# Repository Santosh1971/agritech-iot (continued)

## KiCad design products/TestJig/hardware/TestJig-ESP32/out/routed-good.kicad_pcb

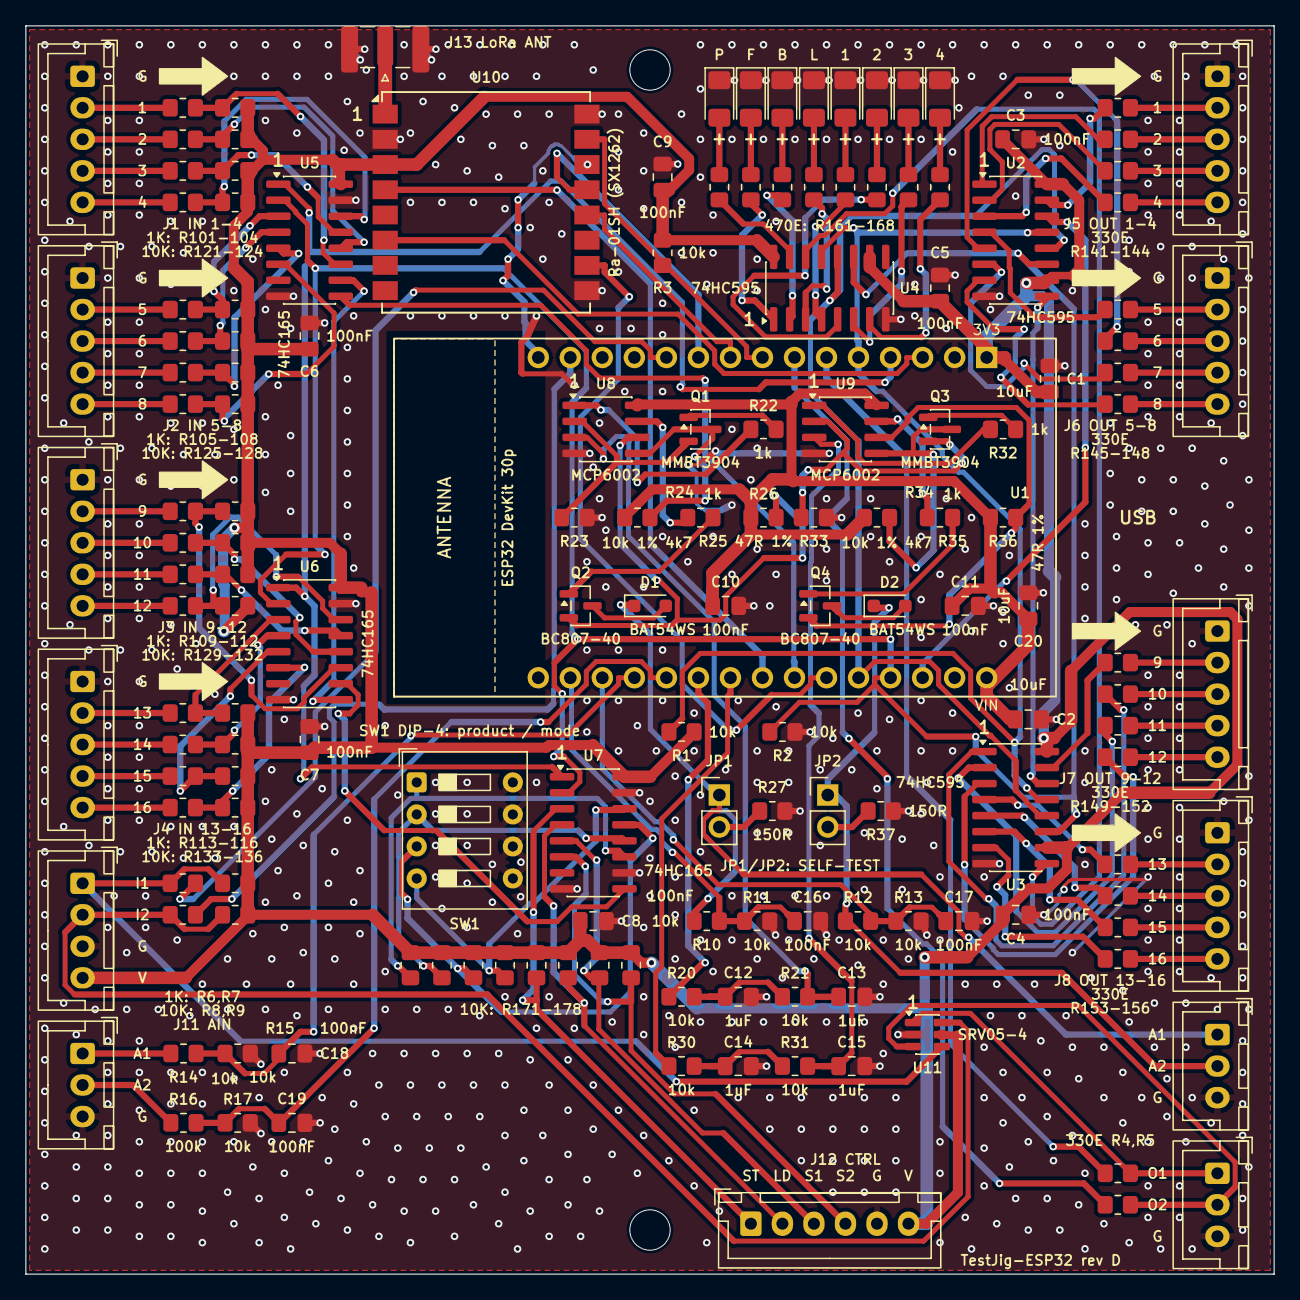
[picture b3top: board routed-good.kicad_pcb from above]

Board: 2 copper layers, 99.0 x 99.0 mm, 161 parts (0 on the bottom side), 149 nets.

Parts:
C1, C2, C20: 10uF; C_0805_2012Metric_Pad1.18x1.45mm_HandSolder
C3, C4, C5, C6, C7, C8, C9, C10, C11, C16, C17, C18, C19: 100nF; C_0805_2012Metric_Pad1.18x1.45mm_HandSolder
C12, C13, C14, C15: 1uF; C_0805_2012Metric_Pad1.18x1.45mm_HandSolder
D1, D2: BAT54WS; D_SOD-323_HandSoldering
D7: PASS Green; LED_1206_3216Metric_Pad1.42x1.75mm_HandSolder
D8: FAIL Red; LED_1206_3216Metric_Pad1.42x1.75mm_HandSolder
D9: BUSY Yellow; LED_1206_3216Metric_Pad1.42x1.75mm_HandSolder
D10: LORA Blue; LED_1206_3216Metric_Pad1.42x1.75mm_HandSolder
D11: USER1 Green; LED_1206_3216Metric_Pad1.42x1.75mm_HandSolder
D12: USER2 Green; LED_1206_3216Metric_Pad1.42x1.75mm_HandSolder
D13: USER3 Green; LED_1206_3216Metric_Pad1.42x1.75mm_HandSolder
D14: USER4 Green; LED_1206_3216Metric_Pad1.42x1.75mm_HandSolder
H1, H2: M3; MountingHole_3.2mm_M3
J1: RLY_SENSE 1-4; JST_XH_B5B-XH-A_1x05_P2.50mm_Vertical
J2: RLY_SENSE 5-8; JST_XH_B5B-XH-A_1x05_P2.50mm_Vertical
J3: RLY_SENSE 9-12; JST_XH_B5B-XH-A_1x05_P2.50mm_Vertical
J4: RLY_SENSE 13-16; JST_XH_B5B-XH-A_1x05_P2.50mm_Vertical
J5: DUT_IN 1-4; JST_XH_B5B-XH-A_1x05_P2.50mm_Vertical
J6: DUT_IN 5-8; JST_XH_B5B-XH-A_1x05_P2.50mm_Vertical
J7: DUT_IN 9-12; JST_XH_B5B-XH-A_1x05_P2.50mm_Vertical
J8: DUT_IN 13-16; JST_XH_B5B-XH-A_1x05_P2.50mm_Vertical
J9: PULSE IN; JST_XH_B4B-XH-A_1x04_P2.50mm_Vertical
J10: 4-20mA OUT; JST_XH_B3B-XH-A_1x03_P2.50mm_Vertical
J11: AIN (AI1 /2, AI2 /11); JST_XH_B3B-XH-A_1x03_P2.50mm_Vertical
J12: JIG_CTRL; JST_XH_B6B-XH-A_1x06_P2.50mm_Vertical
J13: SMA; SMA_Samtec_SMA-J-P-H-ST-EM1_EdgeMount
J14: PULSE OUT; JST_XH_B3B-XH-A_1x03_P2.50mm_Vertical
JP1, JP2: SELFTEST; PinHeader_1x02_P2.54mm_Vertical
Q1, Q3: MMBT3904; SOT-23
Q2, Q4: BC807-40; SOT-23
R1, R2, R3, R8, R9, R10, R11, R12, R13, R14, R15, R17, R20, R21, R30, R31, R121, R122, R123, R124, R125, R126, R127, R128, R129, R130, R131, R132, R133, R134, R135, R136, R171, R172, R173, R174, R175, R176, R177, R178: 10k; R_0805_2012Metric_Pad1.20x1.40mm_HandSolder
R4, R5, R141, R142, R143, R144, R145, R146, R147, R148, R149, R150, R151, R152, R153, R154, R155, R156: 330; R_0805_2012Metric_Pad1.20x1.40mm_HandSolder
R6, R7, R22, R25, R32, R35, R101, R102, R103, R104, R105, R106, R107, R108, R109, R110, R111, R112, R113, R114, R115, R116: 1k; R_0805_2012Metric_Pad1.20x1.40mm_HandSolder
R16: 100k; R_0805_2012Metric_Pad1.20x1.40mm_HandSolder
R23, R33: 10k 1%; R_0805_2012Metric_Pad1.20x1.40mm_HandSolder
R24, R34: 4k7; R_0805_2012Metric_Pad1.20x1.40mm_HandSolder
R26, R36: 47R 1%; R_0805_2012Metric_Pad1.20x1.40mm_HandSolder
R27, R37: 150R; R_0805_2012Metric_Pad1.20x1.40mm_HandSolder
R161, R162, R163, R164, R165, R166, R167, R168: 470; R_0805_2012Metric_Pad1.20x1.40mm_HandSolder
SW1: DIP-4; SW_DIP_SPSTx04_Slide_9.78x12.34mm_W7.62mm_P2.54mm
U1: ESP32 DevKit 30p; ESP32_DevKit_30pin_W25.4mm
U2, U3, U4: 74HC595; SOIC-16_3.9x9.9mm_P1.27mm
U5, U6, U7: 74HC165; SOIC-16_3.9x9.9mm_P1.27mm
U8, U9: MCP6002; SOIC-8_3.9x4.9mm_P1.27mm
U10: Ra-01SH (SX1262); Ai-Thinker-Ra-01-LoRa
U11: SRV05-4; SOT-23-6

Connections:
+3V3: C1.1, C3.1, C4.1, C5.1, C6.1, C7.1, C8.1, C9.1, J9.4, J12.6, R1.2, R3.2, R8.2, R9.2, R121.2, R122.2, R123.2, R124.2, R125.2, R126.2, R127.2, R128.2, R129.2, R130.2, R131.2, R132.2, R133.2, R134.2, R135.2, R136.2, R171.2, R172.2, R173.2, R174.2, R175.2, R176.2, R177.2, R178.2, U1.1, U2.10, U2.16, U3.10, U3.16, U4.10, U4.16, U5.16, U6.16, U7.16, U10.3, U11.5
+5V: C2.1, C10.1, C11.1, C20.1, R24.1, R26.1, R34.1, R36.1, U1.30, U8.8, U9.8
/ADC_AI1: C18.1, R14.2, R15.1, U1.19
/ADC_AI2: C19.1, R16.2, R17.1, U1.20
/ADC_AO1: C16.1, R10.2, R11.1, U1.17
/ADC_AO2: C17.1, R12.2, R13.1, U1.18
/AI1: J11.1, R14.1
/AI2: J11.2, R16.1
/AO1: D1.1, J10.1, JP1.1, R10.1
/AO1_A: Q1.3, R24.2, U8.5
/AO1_B: Q2.2, R26.2, U8.6
/AO1_F1: C12.1, R20.2, R21.1
/AO1_LOAD: JP1.2, R27.1
/AO1_QB1: Q1.1, R22.2
/AO1_QB2: Q2.1, R25.2
/AO1_QC: D1.2, Q2.3
/AO1_QE: Q1.2, R23.1, U8.2
/AO1_U1: R22.1, U8.1
/AO1_U2: R25.1, U8.7
/AO1_VSET: C13.1, R21.2, U8.3
/AO2: D2.1, J10.2, JP2.1, R12.1
/AO2_A: Q3.3, R34.2, U9.5
/AO2_B: Q4.2, R36.2, U9.6
/AO2_F1: C14.1, R30.2, R31.1
/AO2_LOAD: JP2.2, R37.1
/AO2_QB1: Q3.1, R32.2
/AO2_QB2: Q4.1, R35.2
/AO2_QC: D2.2, Q4.3
/AO2_QE: Q3.2, R33.1, U9.2
/AO2_U1: R32.1, U9.1
/AO2_U2: R35.1, U9.7
/AO2_VSET: C15.1, R31.2, U9.3
/DIP1: R171.1, SW1.1, U7.11
/DIP2: R172.1, SW1.2, U7.12
/DIP3: R173.1, SW1.3, U7.13
/DIP4: R174.1, SW1.4, U7.14
/DO1: R141.1, U2.15
/DO2: R142.1, U2.1
/DO3: R143.1, U2.2
/DO4: R144.1, U2.3
/DO5: R145.1, U2.4
/DO6: R146.1, U2.5
/DO7: R147.1, U2.6
/DO8: R148.1, U2.7
/DO9: R149.1, U3.15
/DO10: R150.1, U3.1
/DO11: R151.1, U3.2
/DO12: R152.1, U3.3
/DO13: R153.1, U3.4
/DO14: R154.1, U3.5
/DO15: R155.1, U3.6
/DO16: R156.1, U3.7
/DUT_OUT1: J5.2, R141.2
/DUT_OUT2: J5.3, R142.2
/DUT_OUT3: J5.4, R143.2
/DUT_OUT4: J5.5, R144.2
/DUT_OUT5: J6.2, R145.2
/DUT_OUT6: J6.3, R146.2
/DUT_OUT7: J6.4, R147.2
/DUT_OUT8: J6.5, R148.2
/DUT_OUT9: J7.2, R149.2
/DUT_OUT10: J7.3, R150.2
/DUT_OUT11: J7.4, R151.2
/DUT_OUT12: J7.5, R152.2
/DUT_OUT13: J8.2, R153.2
/DUT_OUT14: J8.3, R154.2
/DUT_OUT15: J8.4, R155.2
/DUT_OUT16: J8.5, R156.2
/LEDA1: D7.2, R161.2
/LEDA2: D8.2, R162.2
/LEDA3: D9.2, R163.2
/LEDA4: D10.2, R164.2
/LEDA5: D11.2, R165.2
/LEDA6: D12.2, R166.2
/LEDA7: D13.2, R167.2
/LEDA8: D14.2, R168.2
/LEDDRV1: R161.1, U4.15
/LEDDRV2: R162.1, U4.1
/LEDDRV3: R163.1, U4.2
/LEDDRV4: R164.1, U4.3
/LEDDRV5: R165.1, U4.4
/LEDDRV6: R166.1, U4.5
/LEDDRV7: R167.1, U4.6
/LEDDRV8: R168.1, U4.7
/LID: J12.2, R176.1, U7.4
/LORA_ANT: J13.1, U10.1
/LORA_BUSY: U1.25, U10.10
/LORA_DIO1: U1.3, U10.6
/LORA_NSS: R3.1, U1.8, U10.15
/LORA_RST: U1.23, U10.4
/PI1: R6.2, U1.11
/PI2: R7.2, U1.14
/PO1: R4.1, U1.6
/PO2: R5.1, U1.7
/PULSE_IN1: J9.1, R6.1, R8.1, U11.4
/PULSE_IN2: J9.2, R7.1, R9.1, U11.6
/PULSE_OUT1: J14.1, R4.2, U11.1
/PULSE_OUT2: J14.2, R5.2, U11.3
/PWM_AO1: R20.1, U1.21
/PWM_AO2: R30.1, U1.22
/RLY_NO1: J1.2, R101.1
/RLY_NO2: J1.3, R102.1
/RLY_NO3: J1.4, R103.1
/RLY_NO4: J1.5, R104.1
/RLY_NO5: J2.2, R105.1
/RLY_NO6: J2.3, R106.1
/RLY_NO7: J2.4, R107.1
/RLY_NO8: J2.5, R108.1
/RLY_NO9: J3.2, R109.1
/RLY_NO10: J3.3, R110.1
/RLY_NO11: J3.4, R111.1
/RLY_NO12: J3.5, R112.1
/RLY_NO13: J4.2, R113.1
/RLY_NO14: J4.3, R114.1
/RLY_NO15: J4.4, R115.1
/RLY_NO16: J4.5, R116.1
/RS1: R101.2, R121.1, U5.11
/RS2: R102.2, R122.1, U5.12
/RS3: R103.2, R123.1, U5.13
/RS4: R104.2, R124.1, U5.14
/RS5: R105.2, R125.1, U5.3
/RS6: R106.2, R126.1, U5.4
/RS7: R107.2, R127.1, U5.5
/RS8: R108.2, R128.1, U5.6
/RS9: R109.2, R129.1, U6.11
/RS10: R110.2, R130.1, U6.12
/RS11: R111.2, R131.1, U6.13
/RS12: R112.2, R132.1, U6.14
/RS13: R113.2, R133.1, U6.3
/RS14: R114.2, R134.1, U6.4
/RS15: R115.2, R135.1, U6.5
/RS16: R116.2, R136.1, U6.6
/SPARE_IN1: J12.3, R177.1, U7.5
/SPARE_IN2: J12.4, R178.1, U7.6
/SPI_MISO: U1.10, U10.13
/SPI_MOSI: U1.15, U10.14
/SPI_SCK: U1.9, U10.12
/SR_CLK: R2.1, U1.27, U2.11, U3.11, U4.11, U5.2, U6.2, U7.2
/SR_D2: U2.9, U3.14
/SR_D3: U3.9, U4.14
/SR_DATA: U1.28, U2.14
/SR_IN: U1.24, U5.9
/SR_LATCH: U1.26, U2.12, U3.12, U4.12
/SR_LOAD: U1.4, U5.1, U6.1, U7.1
/SR_OE: R1.1, U1.5, U2.13, U3.13, U4.13
/SR_Q6: U5.10, U6.9
/SR_Q7: U6.10, U7.9
/START: J12.1, R175.1, U7.3
GND: C1.2, C2.2, C3.2, C4.2, C5.2, C6.2, C7.2, C8.2, C9.2, C10.2, C11.2, C12.2, C13.2, C14.2, C15.2, C16.2, C17.2, C18.2, C19.2, C20.2, D7.1, D8.1, D9.1, D10.1, D11.1, D12.1, D13.1, D14.1, J1.1, J2.1, J3.1, J4.1, J5.1, J6.1, J7.1, J8.1, J9.3, J10.3, J11.3, J12.5, J13.2, J14.3, R2.2, R11.2, R13.2, R15.2, R17.2, R23.2, R27.2, R33.2, R37.2, SW1.5, SW1.6, SW1.7, SW1.8, U1.2, U1.29, U2.8, U3.8, U4.8, U5.8, U5.15, U6.8, U6.15, U7.8, U7.10, U7.15, U8.4, U9.4, U10.2, U10.9, U10.16, U11.2

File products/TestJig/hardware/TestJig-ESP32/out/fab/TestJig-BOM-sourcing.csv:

References,Qty,Value,Footprint,Supplier,Listing,Price (incl GST),Link
"C1, C2, C20",3,10uF,C_0805_2012Metric_Pad1.18x1.45mm_HandSolder,Quartz,10uF 10V X5R 0805 (Kemet),Rs 45 / 20 pcs,https://quartzcomponents.com/products/kemet-10uf-50v-0805-sm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
"C3, C4, C5, C6, C7, C8, C9, C10, C11, C16, C17, C18, C19",13,100nF,C_0805_2012Metric_Pad1.18x1.45mm_HandSolder,Quartz,100nF 50V X7R 0805 (Kemet),Rs 26 / 20 pcs,https://quartzcomponents.com/products/kemet-100nf-50v-0805-s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
"C12, C13, C14, C15",4,1uF,C_0805_2012Metric_Pad1.18x1.45mm_HandSolder,Quartz,1uF 50V X7R 0805,Rs 15 / 5 pcs,https://quartzcomponents.com/products/1uf-1000nf-50v-0805-x7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
"D1, D2",2,BAT54WS,D_SOD-323_HandSoldering,Quartz,BAT54WS SOD-323,Rs 19 / 10 pcs,https://quartzcomponents.com/products/bat54ws-small-signal-s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
D7,1,PASS Green,LED_1206_3216Metric_Pad1.42x1.75mm_HandSolder,Quartz,Green LED 1206,Rs 36 / 50 pcs,https://quartzcomponents.com/products/green-led-smd-1206-pac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
D8,1,FAIL Red,LED_1206_3216Metric_Pad1.42x1.75mm_HandSolder,Quartz,Red LED 1206,Rs 35 / 50 pcs,https://quartzcomponents.com/products/red-led-smd-1206-packa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
D9,1,BUSY Yellow,LED_1206_3216Metric_Pad1.42x1.75mm_HandSolder,Quartz,Yellow LED 1206,Rs 39 / 50 pcs,https://quartzcomponents.com/products/yellow-led-smd-1206-pa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
D10,1,LORA Blue,LED_1206_3216Metric_Pad1.42x1.75mm_HandSolder,Quartz,Blue LED 1206,Rs 32 / 50 pcs,https://quartzcomponents.com/products/blue-led-smd-1206-pack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
D11,1,USER1 Green,LED_1206_3216Metric_Pad1.42x1.75mm_HandSolder,Quartz,Green LED 1206,Rs 36 / 50 pcs,https://quartzcomponents.com/products/green-led-smd-1206-pac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
D12,1,USER2 Green,LED_1206_3216Metric_Pad1.42x1.75mm_HandSolder,Quartz,Green LED 1206,Rs 36 / 50 pcs,https://quartzcomponents.com/products/green-led-smd-1206-pac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
D13,1,USER3 Green,LED_1206_3216Metric_Pad1.42x1.75mm_HandSolder,Quartz,Green LED 1206,Rs 36 / 50 pcs,https://quartzcomponents.com/products/green-led-smd-1206-pac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
D14,1,USER4 Green,LED_1206_3216Metric_Pad1.42x1.75mm_HandSolder,Quartz,Green LED 1206,Rs 36 / 50 pcs,https://quartzcomponents.com/products/green-led-smd-1206-pac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
J1,1,RLY_SENSE 1-4,JST_XH_B5B-XH-A_1x05_P2.50mm_Vertical,Quartz,5-pin JST XH male (vertical),Rs 2 each,https://quartzcomponents.com/products/5-pin-jst-xh-male-conn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
J2,1,RLY_SENSE 5-8,JST_XH_B5B-XH-A_1x05_P2.50mm_Vertical,Quartz,5-pin JST XH male (vertical),Rs 2 each,https://quartzcomponents.com/products/5-pin-jst-xh-male-conn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
J3,1,RLY_SENSE 9-12,JST_XH_B5B-XH-A_1x05_P2.50mm_Vertical,Quartz,5-pin JST XH male (vertical),Rs 2 each,https://quartzcomponents.com/products/5-pin-jst-xh-male-conn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
J4,1,RLY_SENSE 13-16,JST_XH_B5B-XH-A_1x05_P2.50mm_Vertical,Quartz,5-pin JST XH male (vertical),Rs 2 each,https://quartzcomponents.com/products/5-pin-jst-xh-male-conn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
J5,1,DUT_IN 1-4,JST_XH_B5B-XH-A_1x05_P2.50mm_Vertical,Quartz,5-pin JST XH male (vertical),Rs 2 each,https://quartzcomponents.com/products/5-pin-jst-xh-male-conn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
J6,1,DUT_IN 5-8,JST_XH_B5B-XH-A_1x05_P2.50mm_Vertical,Quartz,5-pin JST XH male (vertical),Rs 2 each,https://quartzcomponents.com/products/5-pin-jst-xh-male-conn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
J7,1,DUT_IN 9-12,JST_XH_B5B-XH-A_1x05_P2.50mm_Vertical,Quartz,5-pin JST XH male (vertical),Rs 2 each,https://quartzcomponents.com/products/5-pin-jst-xh-male-conn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
J8,1,DUT_IN 13-16,JST_XH_B5B-XH-A_1x05_P2.50mm_Vertical,Quartz,5-pin JST XH male (vertical),Rs 2 each,https://quartzcomponents.com/products/5-pin-jst-xh-male-conn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
J9,1,PULSE IN,JST_XH_B4B-XH-A_1x04_P2.50mm_Vertical,Quartz,4-pin JST XH male (vertical),Rs 2 each,https://quartzcomponents.com/products/4-pin-jst-xh-male-conn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
J10,1,4-20mA OUT,JST_XH_B3B-XH-A_1x03_P2.50mm_Vertical,Quartz,3-pin JST XH male (vertical),Rs 3 each,https://quartzcomponents.com/products/3-pin-jst-xh-male-conn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
J11,1,"AIN (AI1 /2, AI2 /11)",JST_XH_B3B-XH-A_1x03_P2.50mm_Vertical,Quartz,3-pin JST XH male (vertical),Rs 3 each,https://quartzcomponents.com/products/3-pin-jst-xh-male-conn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
J12,1,JIG_CTRL,JST_XH_B6B-XH-A_1x06_P2.50mm_Vertical,Robu,"JST B6B-XH-A (genuine), SKU R174907",Rs 13 each,https://robu.in/?s=B6B-XH-A&post_type=product
J13,1,SMA,SMA_Samtec_SMA-J-P-H-ST-EM1_EdgeMount,Quartz,"SMA female straight edge mount, 1.6 mm PCB",Rs 22 each,https://quartzcomponents.com/products/sma-female-straight-ed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
J14,1,PULSE OUT,JST_XH_B3B-XH-A_1x03_P2.50mm_Vertical,Quartz,3-pin JST XH male (vertical),Rs 3 each,https://quartzcomponents.com/products/3-pin-jst-xh-male-conn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
"JP1, JP2",2,SELFTEST,PinHeader_1x02_P2.54mm_Vertical,Quartz,Male berg strip 2.54 mm (cut 2 pins) + jumper cap,-,
"Q1, Q3",2,MMBT3904,SOT-23,Quartz,MMBT3904 SOT-23,Rs 3 each,https://quartzcomponents.com/products/mmbt3904-npn-transisto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
"Q2, Q4",2,BC807-40,SOT-23,Quartz,BC807-40 SOT-23,Rs 8 / 5 pcs,https://quartzcomponents.com/products/bc807-40-45-v-500-ma-s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
"R1, R2, R3, R8, R9, R10, R11, R12, R13, R14, R15, R17, R20, R21, R30, R31, R121, R122, R123, R124, R125, R126, R127, R128, R129, R130, R131, R132, R133, R134, R135, R136, R171, R172, R173, R174, R175, R176, R177, R178",40,10k,R_0805_2012Metric_Pad1.20x1.40mm_HandSolder,Quartz,10k 1% 0805,Rs 13 / 20 pcs,https://quartzcomponents.com/products/10k-ohm-103-1-smd-resi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
"R4, R5, R141, R142, R143, R144, R145, R146, R147, R148, R149, R150, R151, R152, R153, R154, R155, R156",18,330,R_0805_2012Metric_Pad1.20x1.40mm_HandSolder,Quartz,330R 1% 0805 (Yageo),Rs 6 / 20 pcs,https://quartzcomponents.com/products/yageo-330-ohm-0805-pac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
"R6, R7, R22, R25, R32, R35, R101, R102, R103, R104, R105, R106, R107, R108, R109, R110, R111, R112, R113, R114, R115, R116",22,1k,R_0805_2012Metric_Pad1.20x1.40mm_HandSolder,Quartz,1k 1% 0805,Rs 18 / 20 pcs,https://quartzcomponents.com/products/1k-ohm-102-1-smd-resis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
R16,1,100k,R_0805_2012Metric_Pad1.20x1.40mm_HandSolder,Quartz,100k 1% 0805 (Yageo),Rs 6 / 20 pcs,https://quartzcomponents.com/products/yageo-100k-ohm-0805-pa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
"R23, R33",2,10k 1%,R_0805_2012Metric_Pad1.20x1.40mm_HandSolder,Quartz,10k 1% 0805,Rs 13 / 20 pcs,https://quartzcomponents.com/products/10k-ohm-103-1-smd-resi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
"R24, R34",2,4k7,R_0805_2012Metric_Pad1.20x1.40mm_HandSolder,Quartz,4k7 5% 0805,Rs 8 / 20 pcs,https://quartzcomponents.com/products/4-7k-4k7-ohm-472-5-smd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
"R26, R36",2,47R 1%,R_0805_2012Metric_Pad1.20x1.40mm_HandSolder,Quartz,47R 1% 0805,Rs 10 / 20 pcs,https://quartzcomponents.com/products/43-ohm-43r-1-smd-resis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
"R27, R37",2,150R,R_0805_2012Metric_Pad1.20x1.40mm_HandSolder,Quartz,150R 1% 0805 (Yageo),Rs 6 / 20 pcs,https://quartzcomponents.com/products/yageo-150-ohm-0805-pac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
"R161, R162, R163, R164, R165, R166, R167, R168",8,470,R_0805_2012Metric_Pad1.20x1.40mm_HandSolder,Quartz,470R 1% 0805 (Yageo),Rs 6 / 20 pcs,https://quartzcomponents.com/products/yageo-470-ohm-0805-pac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
SW1,1,DIP-4,SW_DIP_SPSTx04_Slide_9.78x12.34mm_W7.62mm_P2.54mm,Robu,"4-pos DIP switch THT 2.54 mm (SHOU HAN CJPB-H), SKU R235110",Rs 36 each,https://robu.in/?s=4+position+dip+switch&post_type=product
U1,1,ESP32 DevKit 30p,ESP32_DevKit_30pin_W25.4mm,Quartz,ESP32 30-pin CP2102 DevKit,Rs 375 each,https://quartzcomponents.com/products/esp32-30-pin-developme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
"U2, U3, U4",3,74HC595,SOIC-16_3.9x9.9mm_P1.27mm,Quartz,74HC595 NXP SOIC-16,Rs 9 each,https://quartzcomponents.com/products/74hc595-8-bit-shift-re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
"U5, U6, U7",3,74HC165,SOIC-16_3.9x9.9mm_P1.27mm,Quartz,74HC165 SOIC-16,Rs 14 each,https://quartzcomponents.com/products/74hc165-ic-8-bit-paral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
"U8, U9",2,MCP6002,SOIC-8_3.9x4.9mm_P1.27mm,Quartz,MCP6002-I/SN SOIC-8,Rs 44 each,https://quartzcomponents.com/products/mcp6002-i-sn-microchip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
U10,1,Ra-01SH (SX1262),Ai-Thinker-Ra-01-LoRa,WM1 source,"ISC-SX1262-B / Ra-01SH, same module as WM1-Pro",-,Not checked on Quartz/Robu; Quartz LRTC-1262 is SX1262 but a different pinout
U11,1,SRV05-4,SOT-23-6,Quartz,SRV05-4 SOT-23-6,Rs 7 each,https://quartzcomponents.com/products/srv05-4-esd-protection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
-,2,15-pin female header 2.54 mm (cut from 40-pin strip),-,Quartz,40-pin female berg strip,Rs 10 each,https://quartzcomponents.com/products/40-pin-straight-female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
-,4,M3 x 10 mm standoff + screw,-,any,,,

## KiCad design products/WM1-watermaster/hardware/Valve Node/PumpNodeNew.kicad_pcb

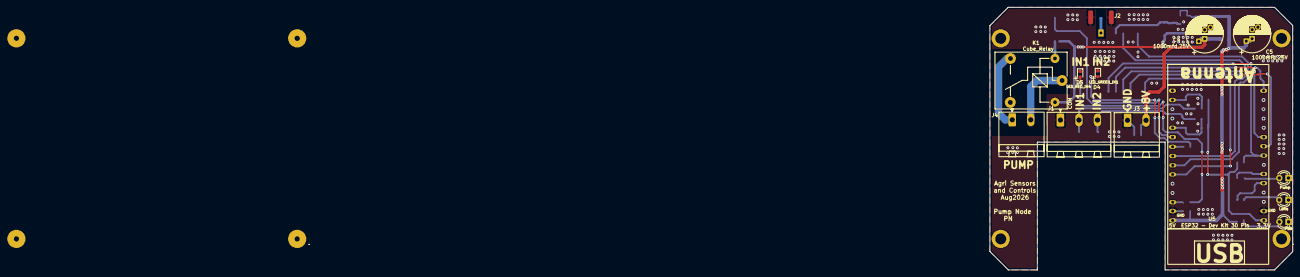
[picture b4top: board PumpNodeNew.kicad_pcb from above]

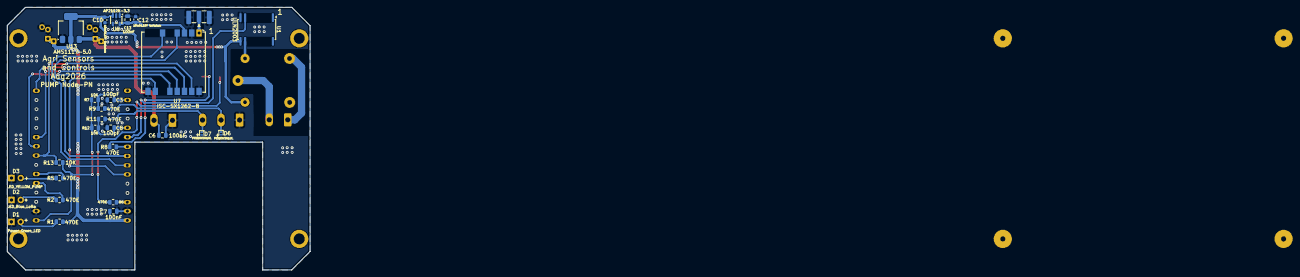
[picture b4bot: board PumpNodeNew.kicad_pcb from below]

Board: 2 copper layers, 83.0 x 72.0 mm, 39 parts (24 on the bottom side), 30 nets.

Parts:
., .#2: MountingHole; MountingHole_3.2mm_M3
C3, C8: 100pF; C_0805_2012Metric
C4, C5: 1000mfd,25V; CP_Radial_D10.0mm_P2.50mm_P5.00mm
C6, C7, C13: 100nF; C_0805_2012Metric
C10, C12: 10mfd,10V tentalum; C_0603_1608Metric
D1: Power_Green_LED; LED_D3.0mm
D2: LED_Blue_LoRa; LED_D3.0mm
D3: LED_YELLOW_PUMP; LED_D3.0mm
D4: LED_GREEN_IN1; LED_0603_1608Metric
D5: LED_RED_IN4; LED_0603_1608Metric
D6, D7: PESD3V3U1UL; D_SOD-882
H1: MountingHole; MountingHole_3.2mm_M3
J1: Conn_IN; PhoenixContact_MSTBA_2,5_3-G-5,08_1x03_P5.08mm_Horizontal
J2: Conn_Coaxial_Small; SMA_Samtec_SMA-J-P-H-ST-EM1_EdgeMount
J3: PWR_CONN; PhoenixContact_MSTBA_2,5_2-G-5,08_1x02_P5.08mm_Horizontal
J4: Relay_CONN; PhoenixContact_MSTBA_2,5_2-G-5,08_1x02_P5.08mm_Horizontal
K1: Cube_Relay; Relay_SPDT_SANYOU_SRD_Series_Form_C
R1, R2, R5, R6, R8, R9, R11: 470E; R_0805_2012Metric
R7, R12, R13: 10K; R_0805_2012Metric
U1: ULN2003; SOIC-16W_5.3x10.2mm_P1.27mm
U5: ESP32 30 Pin CP2102 Development Board; ESP32-C3-DevKitM-1
U7: ISC-SX1262-B; Ai-Thinker-Ra-01-LoRa
U8: AP2112K-3.3; SOT-23-5
U13: AMS1117-5.0; SOT-223-3_TabPin2

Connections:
+3.3V: R7.1, R12.1, R13.1, U5.1 (3V3_Out)
+3.3VL: C12.1, C13.1, U7.3 (VDD), U8.5 (VOUT)
+5V: C5.1, C7.1, C10.1, K1.5, R1.1, U1.9 (COM), U5.30 (VIN/5V_Power_IN), U8.1 (VIN), U8.3 (EN), U13.2 (VO)
+8V: C4.1, C6.1, J3.2, U13.3 (VI)
/BUSY: U5.25 (D27), U7.10 (DIO4/BUSY)
/DIO1: U5.24 (D26), U7.6 (DIO1)
/IN1_CON: D6.1 (K), J1.2, R9.2
/IN1_LED_MCU: R8.1, U5.22 (D33)
/IN1_MCU: C3.1, R7.2, R9.1, U5.17 (VP(36)/Input_only)
/IN4_CON: D7.1 (K), J1.3, R11.2
/IN4_LED_MCU: R6.1, U5.28 (D13)
/IN4_MCU: C8.1, R11.1, R12.2, U5.20 (D35/Input_only)
/LoRa_LED: R2.1, U5.5 (D4)
/MISO: U5.10 (D19), U7.13 (MISO)
/MOSI: U5.15 (D23), U7.14 (MOSI)
/NSS: R13.2, U5.8 (D5/BootSensitive), U7.15 (~NSS)
/Pump_ON_Yellow_LED: R5.1, U5.6 (Rx2/D16)
/RELAY1_COIL: K1.2, U1.10 (O7)
/RELAY1_MCU: U1.7 (I7), U5.21 (D32)
/RESET: U5.23 (D25), U7.4 (~RESET)
/RL1_CON_1: J4.2, K1.1
/RLY_COMM: J4.1, K1.3
/SCK: U5.9 (D18), U7.12 (SCK)
GND: C3.2, C4.2, C5.2, C6.2, C7.2, C8.2, C10.2, C12.2, C13.2, D1.1 (K), D2.1 (K), D3.1 (K), D4.1 (K), D5.1 (K), D6.2 (A), D7.2 (A), J1.1, J2.2 (Ext), J3.1, U1.8 (GND), U5.2 (GND), U5.29 (GND), U7.2 (GND), U7.9 (GND), U7.16 (GND), U8.2 (GND), U13.1 (GND)
unnamed: D1.2 (A), R1.2
unnamed: D2.2 (A), R2.2
unnamed: D3.2 (A), R5.2
unnamed: D4.2 (A), R8.2
unnamed: D5.2 (A), R6.2
unnamed: J2.1 (In), U7.1 (ANT)
